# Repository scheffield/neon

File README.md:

# Neon

Neon is a remote controllable RGB light meant for video shots and life streaming. It's build around the ESP32-S2 and addressable RGB lights like the WS2812 or SK6812. This repository contains all the files to build your own version.

If you haven't go check out the build and some more info in this YouTube video:

## Directory structure
```
$project_root/
├── cad/ ........... open with Fusion360
├── code/
│   ├── baords/ .... board config
│   ├── data/ ...... compiled website
│   ├── src/ ....... code for ESP32
│   ├── variants ... particion table
│   └── web/ ....... web UI
├── pcb/ ........... open with KiCad
└── stl/ ........... for 3D printing
```

## Web UI

### setup
```bash
cd web
npm i
```

### develop
```bash
npm run dev
```

### build
```bash
npm run webpack
cp dist/index.html ../data
pio run --target uploadfs
```

The last step is assuming that PlatformIO is installed and available as `pio`.

## BOM
Appart from the BOM for the PCB which can be exported from KiCad, the following parts are needed:

**BOM**
| Part | Amount |
|---|---|
| [1/4"*20 Threaded Heat Set Inserts](https://www.amazon.com.au/dp/B077P4M1CM) | 1 |
| [3-pin LiPo Battery 6000mAh](https://core-electronics.com.au/3-pin-lipo-battery-for-pijuice-6000mah.html) | 1 |

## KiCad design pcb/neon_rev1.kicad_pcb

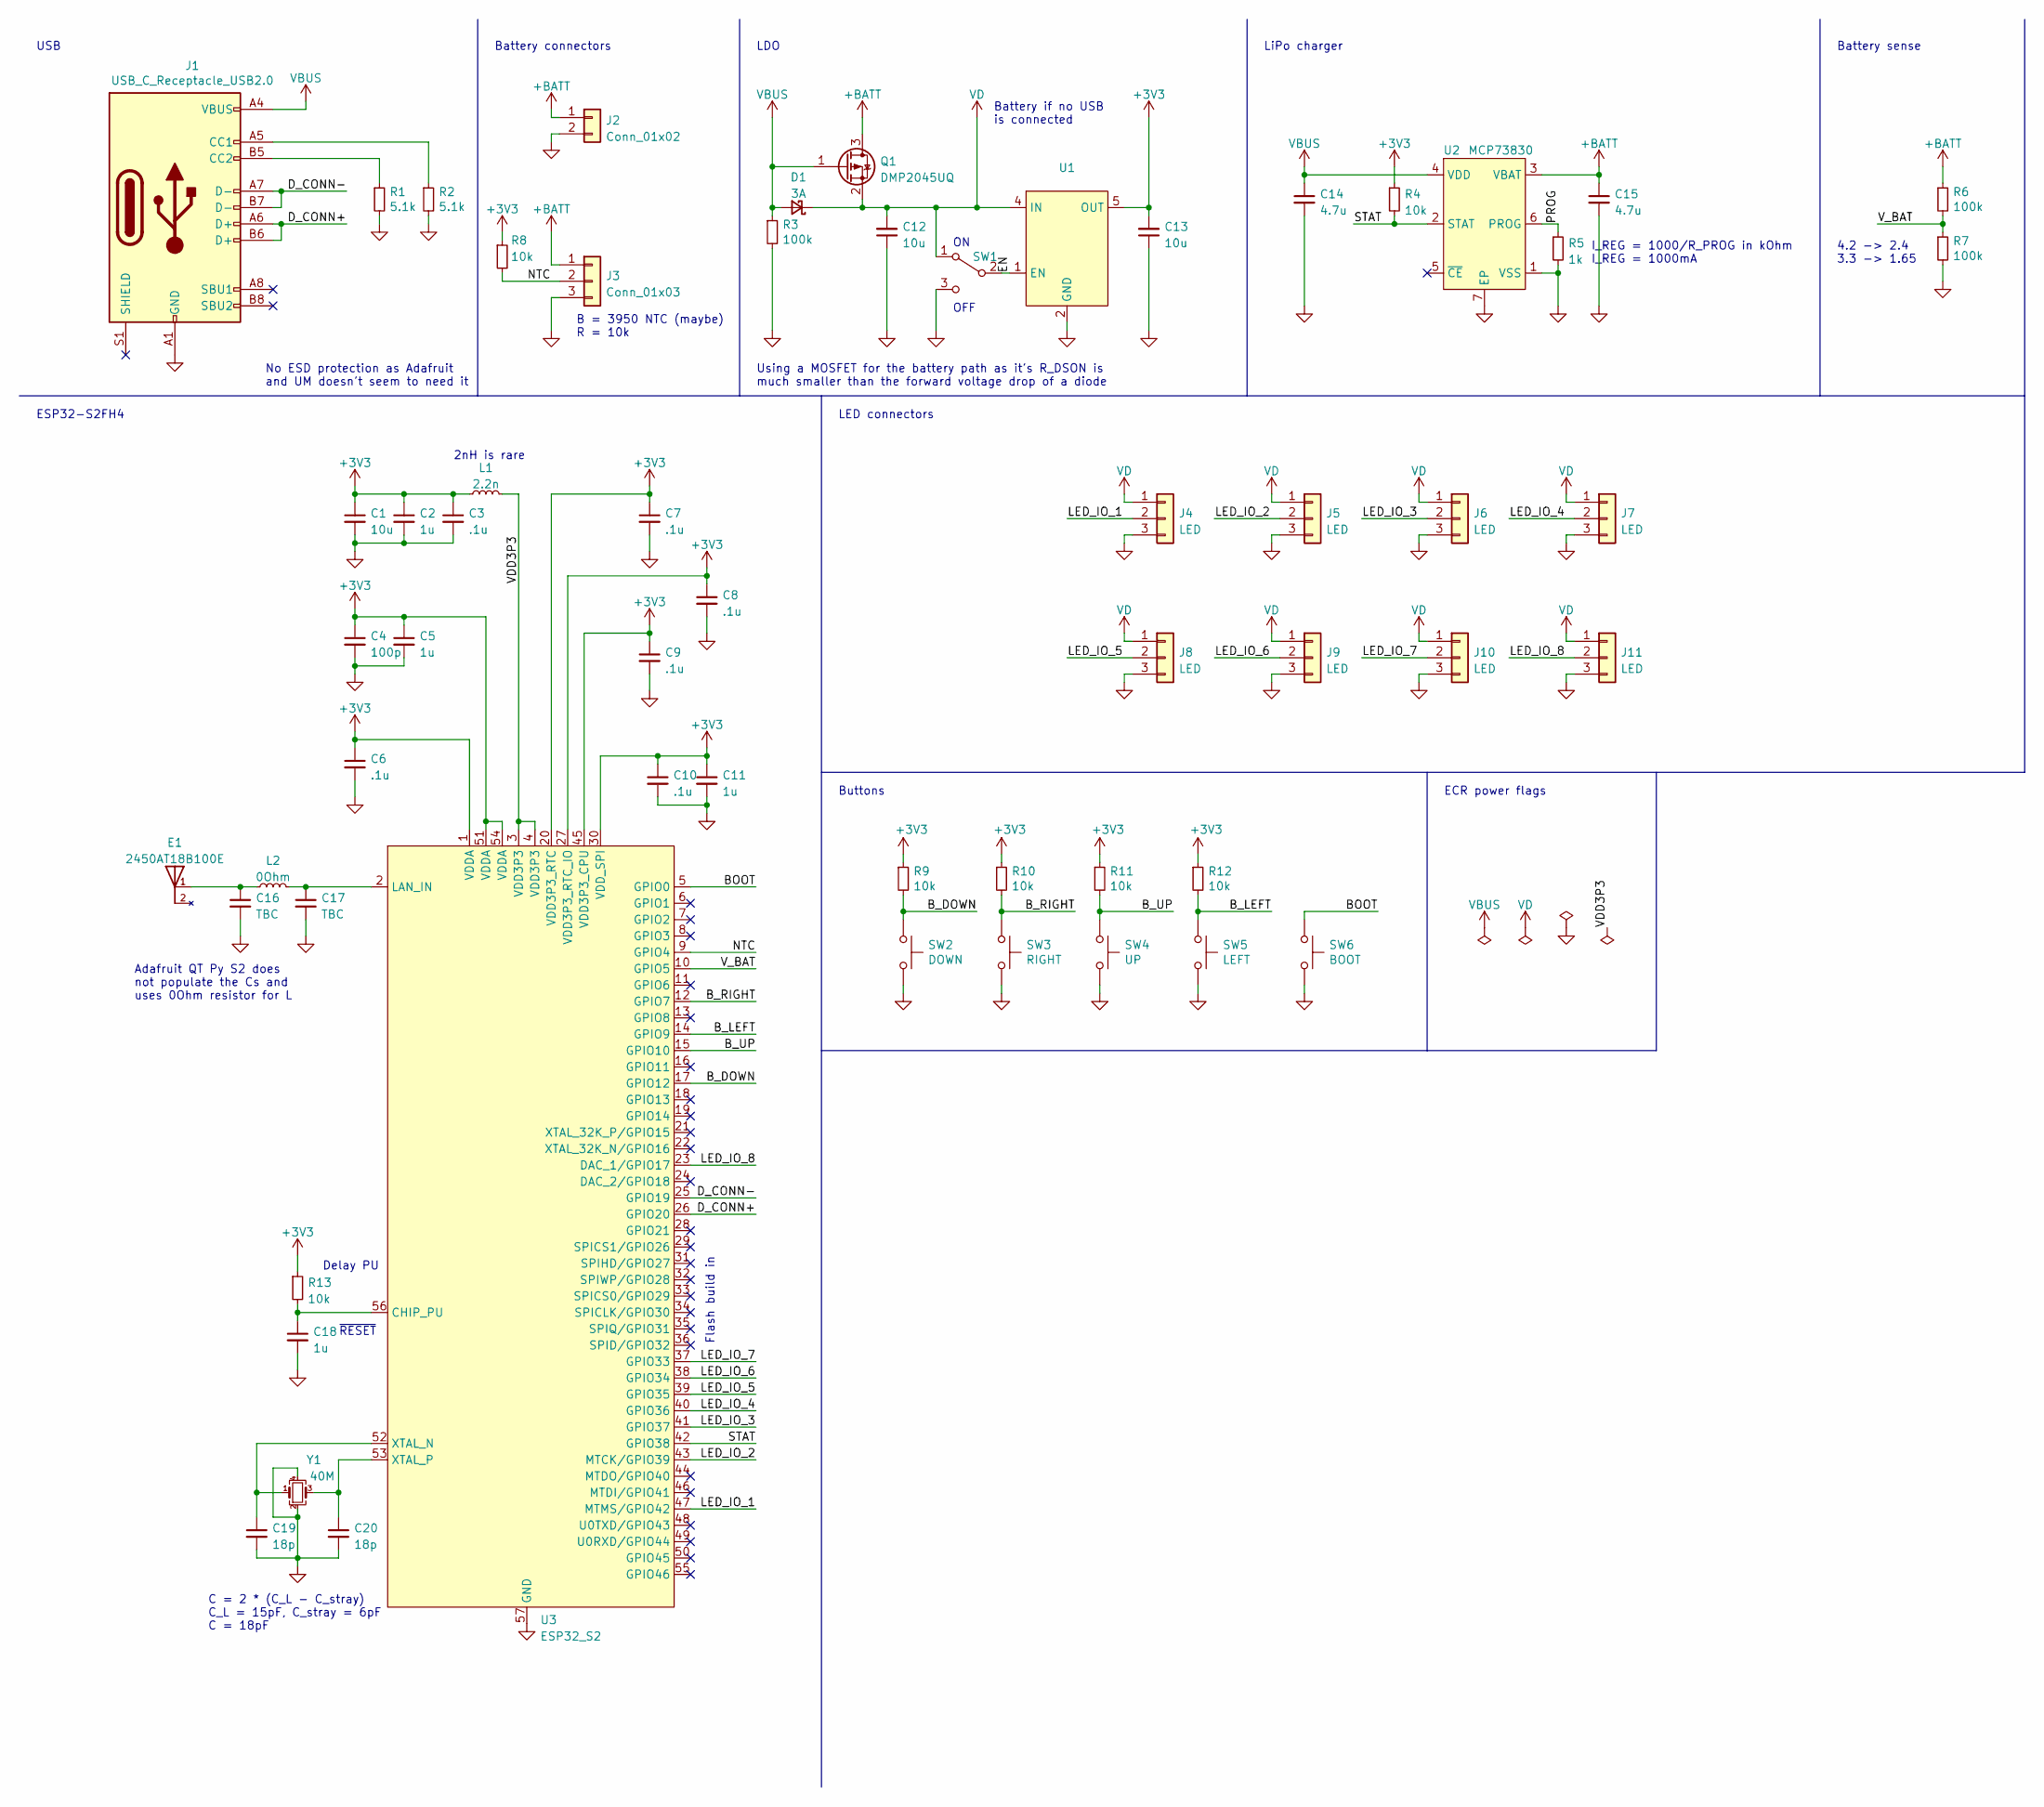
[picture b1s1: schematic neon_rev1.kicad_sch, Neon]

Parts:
C1, C12, C13: 10u; C_0603_1608Metric
C2, C5, C11, C18: 1u; C_0603_1608Metric
C3, C6, C7, C8, C9, C10: .1u; C_0603_1608Metric
C4: 100p; C_0603_1608Metric
C14, C15: 4.7u; C_0603_1608Metric
C16, C17: TBC; C_0402_1005Metric
C19, C20: 18p; C_0603_1608Metric
D1: 3A; D_PowerDI-123
E1: 2450AT18B100E; XDCR_2450AT18B100E; PARTREV 4.0
J1: USB_C_Receptacle_USB2.0; USB_C_Receptacle_Palconn_UTC16-G
J2: Conn_01x02; JST_PH_S2B-PH-SM4-TB_1x02-1MP_P2.00mm_Horizontal
J3: Conn_01x03; JST_PH_S3B-PH-SM4-TB_1x03-1MP_P2.00mm_Horizontal
J4, J5, J6, J7, J8, J9, J10, J11: LED; LED_strip
L1: 2.2n; L_0603_1608Metric
L2: 0Ohm; L_0402_1005Metric
Q1: DMP2045UQ; SOT-23
R1, R2: 5.1k; R_0603_1608Metric
R3, R6, R7: 100k; R_0603_1608Metric
R4, R8, R9, R10, R11, R12, R13: 10k; R_0603_1608Metric
R5: 1k; R_0603_1608Metric
SW1: POWER; SW_SPDT_CK-JS102011SAQN
SW2: DOWN; SW_SPST_PTS645
SW3: RIGHT; SW_SPST_PTS645
SW4: UP; SW_SPST_PTS645
SW5: LEFT; SW_SPST_PTS645
SW6: BOOT; SW_SPST_PTS815
U1: (no value)
U2: MCP73830; TDFN-6-1EP_2x2mm_P0.5mm_EP0.6x1.6mm
U3: ESP32_S2; ESP32-S2
Y1: 40M; Crystal_SMD_3225-4Pin_3.2x2.5mm

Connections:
+3V3: C1.1, C2.1, C3.1, C4.1, C5.1, C6.1, C7.1, C8.1, C9.1, C10.1, C11.1, C13.2, L1.1, R4.1, R8.1, R9.1, R10.1, R11.1, R12.1, R13.1, U1.5 (OUT), U3.1 (VDDA), U3.20 (VDD3P3_RTC), U3.27 (VDD3P3_RTC_IO), U3.30 (VDD_SPI), U3.45 (VDD3P3_CPU), U3.51 (VDDA), U3.54 (VDDA)
+BATT: C15.1, J2.1, J3.1, Q1.3 (D), R6.1, U2.3 (VBAT)
/BOOT: SW6.1, U3.5 (GPIO0)
/B_DOWN: R9.2, SW2.1, U3.17 (GPIO12)
/B_LEFT: R12.2, SW5.1, U3.14 (GPIO9)
/B_RIGHT: R10.2, SW3.1, U3.12 (GPIO7)
/B_UP: R11.2, SW4.1, U3.15 (GPIO10)
/D_CONN+: J1.A6 (D+), J1.B6 (D+), U3.26 (GPIO20)
/D_CONN-: J1.A7 (D-), J1.B7 (D-), U3.25 (GPIO19)
/EN: SW1.2 (B), U1.1 (EN)
/LED_IO_1: J4.2, U3.47 (MTMS/GPIO42)
/LED_IO_2: J5.2, U3.43 (MTCK/GPIO39)
/LED_IO_3: J6.2, U3.41 (GPIO37)
/LED_IO_4: J7.2, U3.40 (GPIO36)
/LED_IO_5: J8.2, U3.39 (GPIO35)
/LED_IO_6: J9.2, U3.38 (GPIO34)
/LED_IO_7: J10.2, U3.37 (GPIO33)
/LED_IO_8: J11.2, U3.23 (DAC_1/GPIO17)
/NTC: J3.2, R8.2, U3.9 (GPIO4)
/PROG: R5.1, U2.6 (PROG)
/STAT: R4.2, U2.2 (STAT), U3.42 (GPIO38)
/VDD3P3: L1.2, U3.3 (VDD3P3), U3.4 (VDD3P3)
/V_BAT: R6.2, R7.1, U3.10 (GPIO5)
GND: C1.2, C2.2, C3.2, C4.2, C5.2, C6.2, C7.2, C8.2, C9.2, C10.2, C11.2, C12.1, C13.1, C14.2, C15.2, C16.2, C17.2, C18.2, C19.2, C20.2, J1.A1 (GND), J1.A12 (GND), J1.B1 (GND), J1.B12 (GND), J2.2, J3.3, J4.3, J5.3, J6.3, J7.3, J8.3, J9.3, J10.3, J11.3, R1.2, R2.2, R3.2, R5.2, R7.2, SW1.3 (C), SW2.2, SW3.2, SW4.2, SW5.2, SW6.2, U1.2 (GND), U2.1 (VSS), U2.7 (EP), U3.57 (GND), Y1.2, Y1.4
unnamed: C16.1, E1.1, L2.1
unnamed: C17.1, L2.2, U3.2 (LAN_IN)
unnamed: C18.1, R13.2, U3.56 (CHIP_PU)
unnamed: C19.1, U3.52 (XTAL_N), Y1.1
unnamed: C20.1, U3.53 (XTAL_P), Y1.3
unnamed: J1.A5 (CC1), R2.1
unnamed: J1.B5 (CC2), R1.1
VBUS: C14.1, D1.2 (A), J1.A4 (VBUS), J1.A9 (VBUS), J1.B4 (VBUS), J1.B9 (VBUS), Q1.1 (G), R3.1, U2.4 (VDD)
VD: C12.2, D1.1 (K), J4.1, J5.1, J6.1, J7.1, J8.1, J9.1, J10.1, J11.1, Q1.2 (S), SW1.1 (A), U1.4 (IN)

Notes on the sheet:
4.2 -> 2.4 3.3 -> 1.65
Battery sense
ECR power flags
~{RESET}
Flash build in
Battery if no USB is connected
LDO
LED connectors
I_REG = 1000/R_PROG in kOhm I_REG = 1000mA
Battery connectors
Using a MOSFET for the battery path as it's R_DSON is much smaller than the forward voltage drop of a diode
OFF
ESP32-S2FH4
2nH is rare
Buttons
LiPo charger
B = 3950 NTC (maybe) R = 10k
No ESD protection as Adafruit and UM doesn't seem to need it
USB
C = 2 * (C_L - C_stray) C_L = 15pF, C_stray = 6pF C = 18pF
Adafruit QT Py S2 does not populate the Cs and uses 0Ohm resistor for L
Delay PU

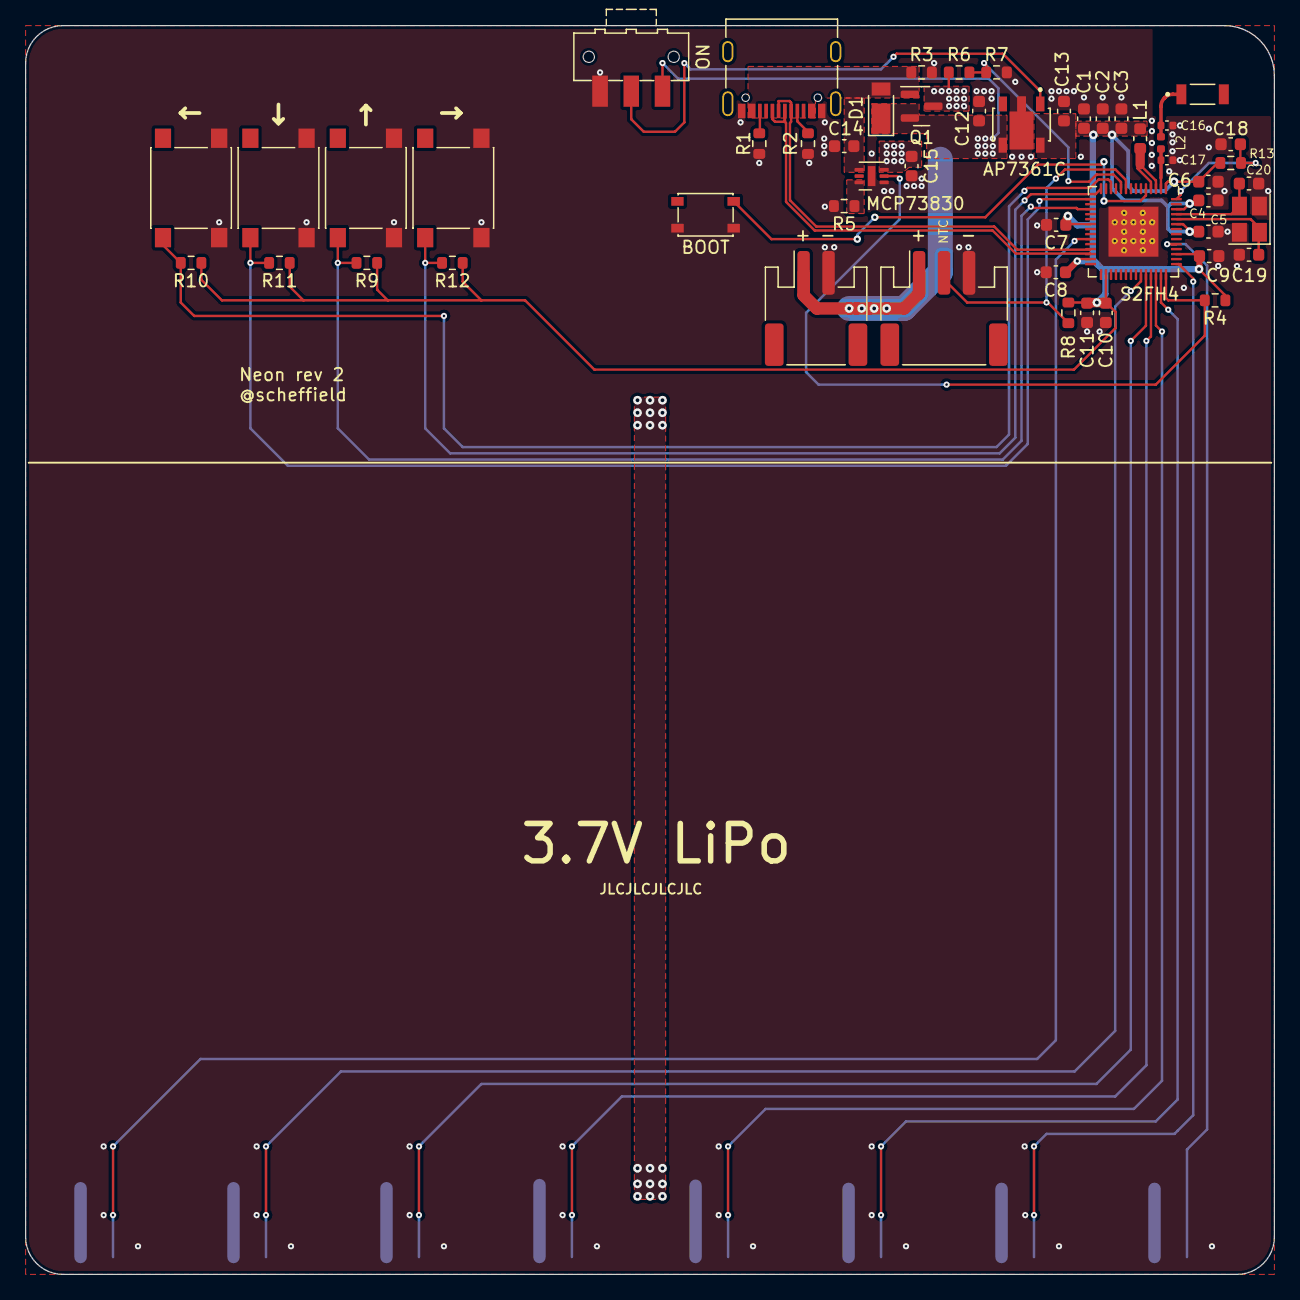
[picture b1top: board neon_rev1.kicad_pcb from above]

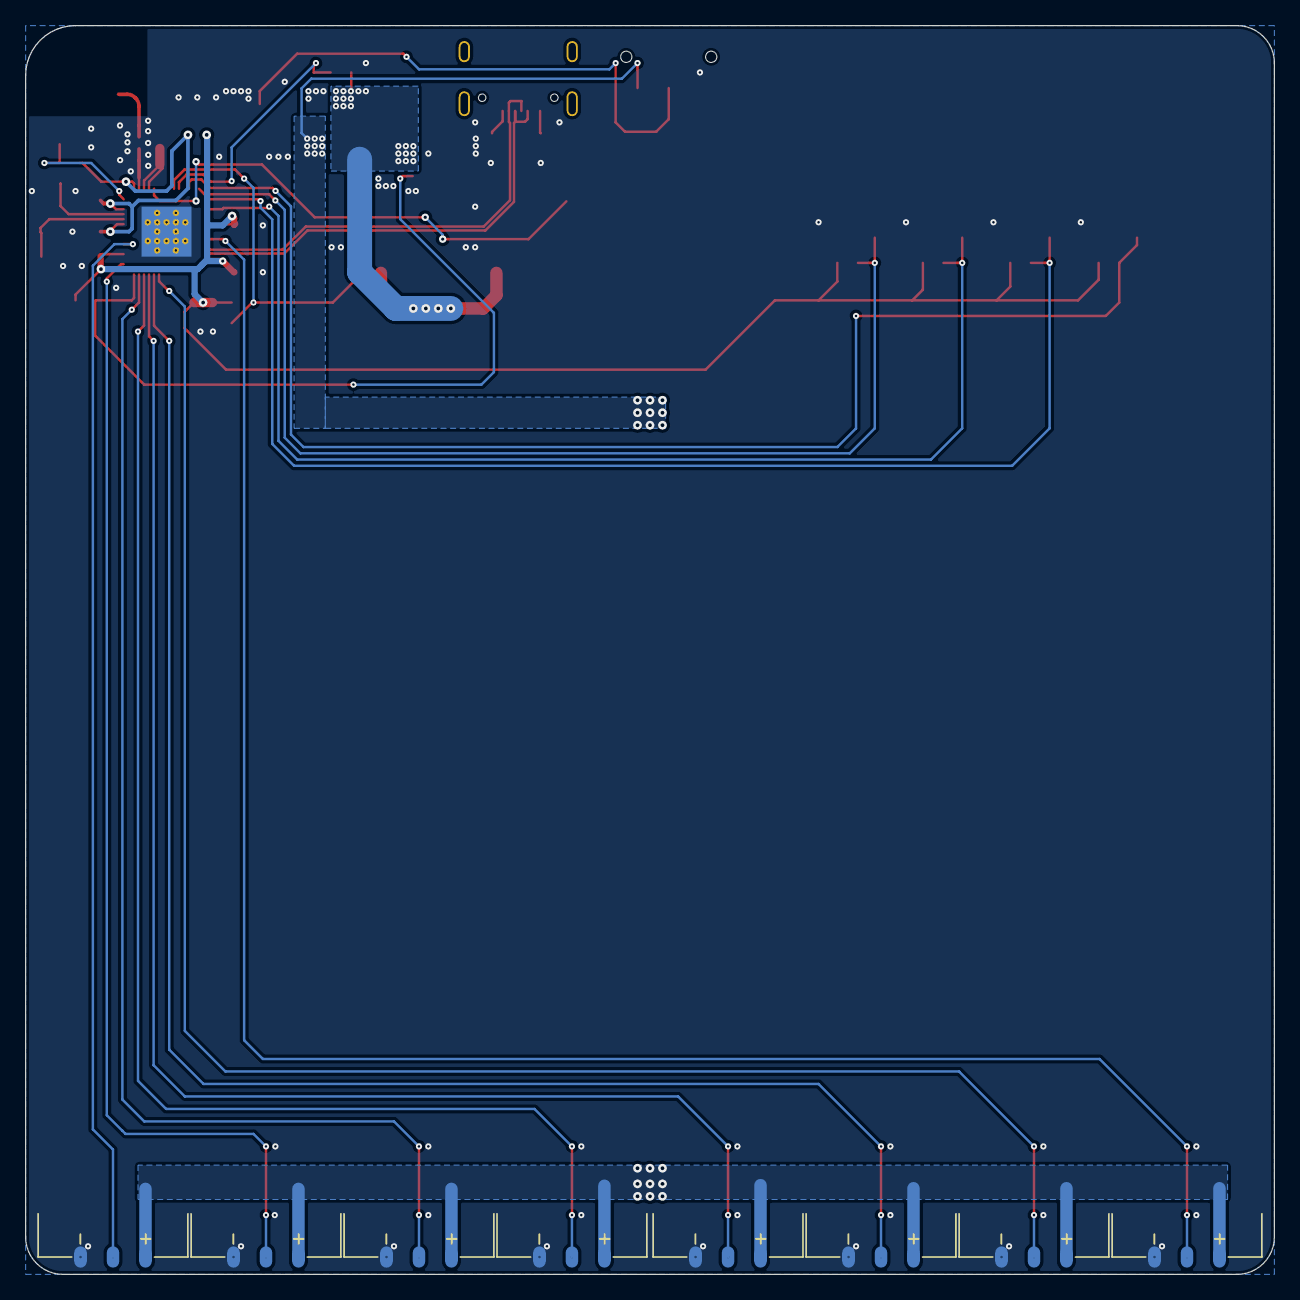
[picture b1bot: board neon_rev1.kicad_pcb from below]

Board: 4 copper layers, 100.0 x 100.0 mm, 59 parts (8 on the bottom side), 33 nets.

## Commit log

2023-01-22 CAD and STL
2023-01-22 code
2023-01-22 readme
2023-01-28 Using SK6812 with RGBW
